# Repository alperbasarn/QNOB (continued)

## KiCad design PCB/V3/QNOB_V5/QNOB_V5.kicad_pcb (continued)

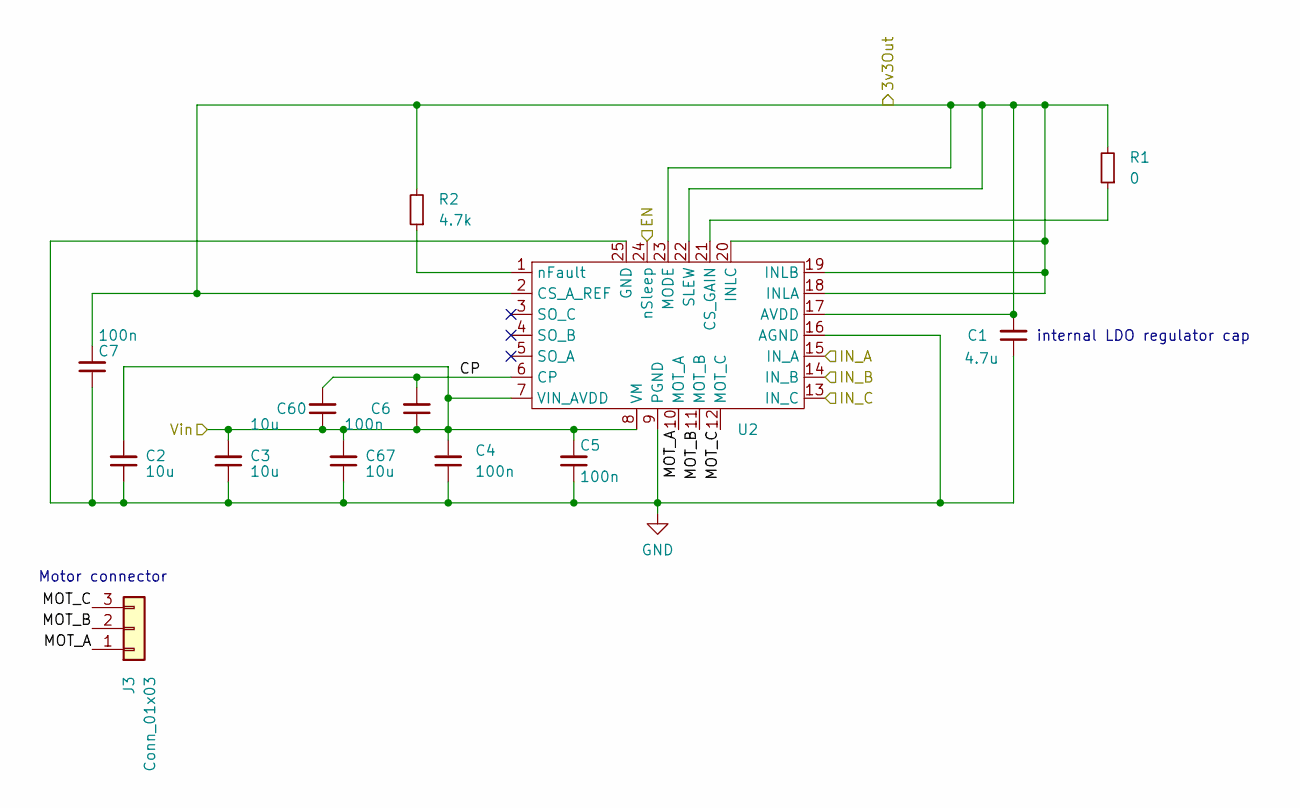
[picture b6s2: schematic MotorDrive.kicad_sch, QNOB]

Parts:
C1: 4.7u; C_0603_1608Metric_Pad1.08x0.95mm_HandSolder
C2, C3, C60: 10u; C_0603_1608Metric_Pad1.08x0.95mm_HandSolder
C4, C5, C6, C7: 100n; C_0603_1608Metric_Pad1.08x0.95mm_HandSolder
C67: 10u; CP_EIA-1608-08_AVX-J_Pad1.25x1.05mm_HandSolder
J3: Conn_01x03; Molex_PicoBlade_53048-0310_1x03_P1.25mm_Horizontal
R1: 0; R_0603_1608Metric_Pad0.98x0.95mm_HandSolder
R2: 4.7k; R_0603_1608Metric_Pad0.98x0.95mm_HandSolder
U2: IC_DRV8311HRRWR

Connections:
/GPIO5: U2.24 (nSleep); also elsewhere on the board
/GPIO6: U2.13 (IN_C); also elsewhere on the board
/GPIO7: U2.14 (IN_B); also elsewhere on the board
/GPIO8: U2.15 (IN_A); also elsewhere on the board
/Motor drive/CP: C6.2, C60.2, U2.6 (CP)
/Motor drive/MOT_A: J3.1, U2.10 (MOT_A)
/Motor drive/MOT_B: J3.2, U2.11 (MOT_B)
/Motor drive/MOT_C: J3.3, U2.12 (MOT_C)
DRV8311_3v3: C1.2, C7.2, R1.2, R2.2, U2.2 (CS_A_REF), U2.17 (AVDD), U2.18 (INLA), U2.19 (INLB), U2.20 (INLC), U2.22 (SLEW), U2.23 (MODE); also elsewhere on the board
GND: C1.1, C2.1, C3.1, C4.1, C5.1, C7.1, C67.1, U2.9 (PGND), U2.16 (AGND), U2.25 (GND); also elsewhere on the board
unnamed: R1.1, U2.21 (CS_GAIN)
unnamed: R2.1, U2.1 (nFault)
VSYS_PROTECTED: C2.2, C3.2, C4.2, C5.2, C6.1, C60.1, C67.2, U2.7 (VIN_AVDD), U2.8 (VM); also elsewhere on the board

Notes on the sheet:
Motor connector
internal LDO regulator cap

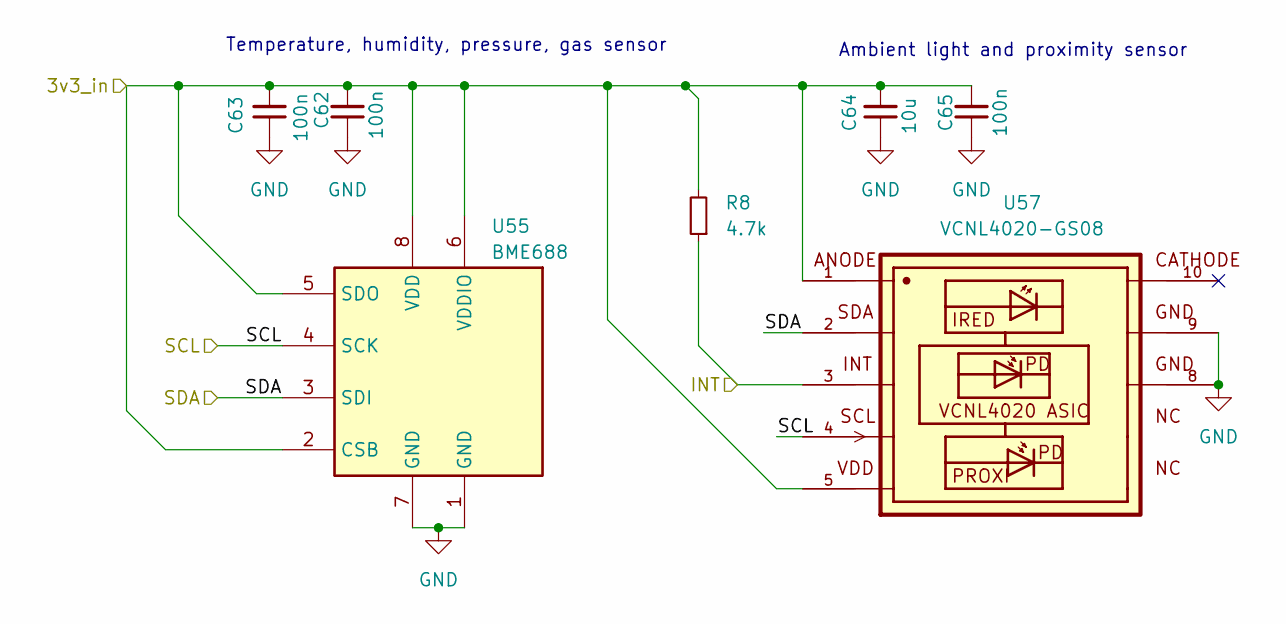
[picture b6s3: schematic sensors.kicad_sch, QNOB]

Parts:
C62, C63: 100n; C_0402_1005Metric
C64: 10u; C_0603_1608Metric_Pad1.08x0.95mm_HandSolder
C65: 100n; C_0603_1608Metric_Pad1.08x0.95mm_HandSolder
R8: 4.7k; R_0603_1608Metric_Pad0.98x0.95mm_HandSolder
U55: BME688; Bosch_LGA-8_3x3mm_P0.8mm_ClockwisePinNumbering
U57: VCNL4020-GS08; PHODET_VCNL4020

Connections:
3V3_Protected: C62.2, C63.2, C64.2, C65.2, R8.2, U55.2 (CSB), U55.5 (SDO), U55.6 (VDDIO), U55.8 (VDD), U57.1, U57.5; also elsewhere on the board
/GPIO1: R8.1, U57.3; also elsewhere on the board
/GPIO20: U55.4 (SCK), U57.4; also elsewhere on the board
/GPIO21: U55.3 (SDI), U57.2; also elsewhere on the board
GND: C62.1, C63.1, C64.1, C65.1, U55.1 (GND), U55.7 (GND), U57.8, U57.9; also elsewhere on the board

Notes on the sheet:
Ambient light and proximity sensor
Temperature, humidity, pressure, gas sensor

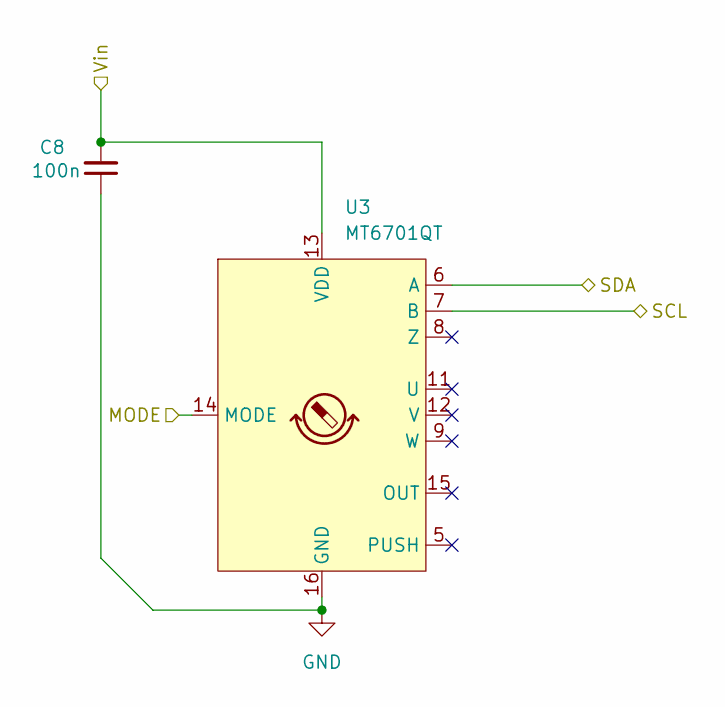
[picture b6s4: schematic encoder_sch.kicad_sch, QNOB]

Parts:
C8: 100n; C_0402_1005Metric
U3: MT6701QT; QFN-16-1EP_3x3mm_P0.5mm_EP1.7x1.7mm

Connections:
/ENC_POWER: C8.2, U3.13 (VDD); also elsewhere on the board
/GPIO20: U3.7 (B); also elsewhere on the board
/GPIO21: U3.6 (A); also elsewhere on the board
/encoder/MODE: U3.14 (MODE); also elsewhere on the board
GND: C8.1, U3.16 (GND), U3.17 (GND); also elsewhere on the board

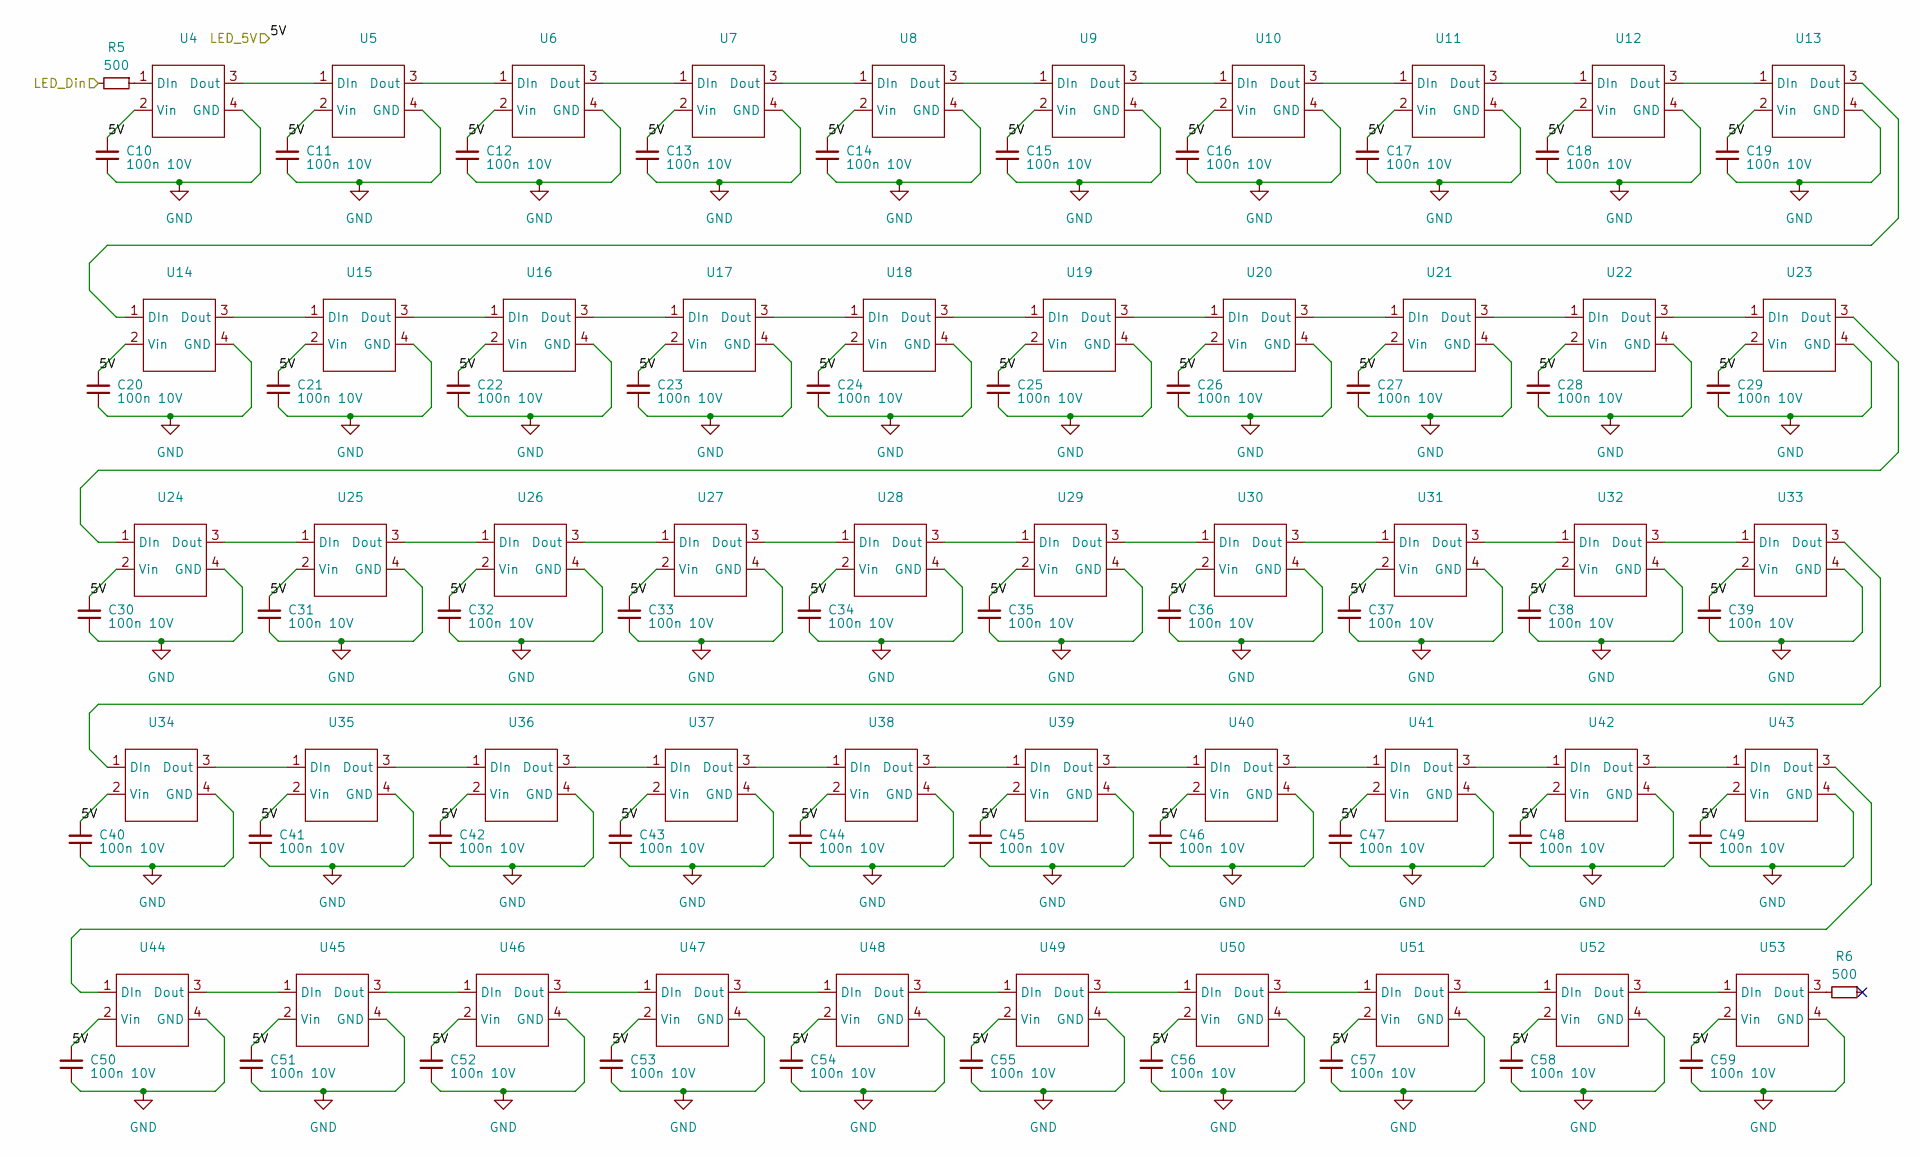
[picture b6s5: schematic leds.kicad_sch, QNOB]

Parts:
C10, C11, C12, C13, C14, C15, C16, C17, C18, C19, C20, C21, C22, C23, C24, C25, C26, C27, C28, C29, C30, C31, C32, C33, C34, C35, C36, C37, C38, C39, C40, C41, C42, C43, C44, C45, C46, C47, C48, C49, C50, C51, C52, C53, C54, C55, C56, C57, C58, C59: 100n 10V; C_0402_1005Metric
R5, R6: 500; R_0402_1005Metric
U4, U5, U6, U7, U8, U9, U10, U11, U12, U13, U14, U15, U16, U17, U18, U19, U20, U21, U22, U23, U24, U25, U26, U27, U28, U29, U30, U31, U32, U33, U34, U35, U36, U37, U38, U39, U40, U41, U42, U43, U44, U45, U46, U47, U48, U49, U50, U51, U52, U53: SK6805-EC15

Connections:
/leds/LED_Din: R5.2; also elsewhere on the board
GND: C10.1, C11.1, C12.1, C13.1, C14.1, C15.1, C16.1, C17.1, C18.1, C19.1, C20.1, C21.1, C22.1, C23.1, C24.1, C25.1, C26.1, C27.1, C28.1, C29.1, C30.1, C31.1, C32.1, C33.1, C34.1, C35.1, C36.1, C37.1, C38.1, C39.1, C40.1, C41.1, C42.1, C43.1, C44.1, C45.1, C46.1, C47.1, C48.1, C49.1, C50.1, C51.1, C52.1, C53.1, C54.1, C55.1, C56.1, C57.1, C58.1, C59.1, U4.4 (GND), U5.4 (GND), U6.4 (GND), U7.4 (GND), U8.4 (GND), U9.4 (GND), U10.4 (GND), U11.4 (GND), U12.4 (GND), U13.4 (GND), U14.4 (GND), U15.4 (GND), U16.4 (GND), U17.4 (GND), U18.4 (GND), U19.4 (GND), U20.4 (GND), U21.4 (GND), U22.4 (GND), U23.4 (GND), U24.4 (GND), U25.4 (GND), U26.4 (GND), U27.4 (GND), U28.4 (GND), U29.4 (GND), U30.4 (GND), U31.4 (GND), U32.4 (GND), U33.4 (GND), U34.4 (GND), U35.4 (GND), U36.4 (GND), U37.4 (GND), U38.4 (GND), U39.4 (GND), U40.4 (GND), U41.4 (GND), U42.4 (GND), U43.4 (GND), U44.4 (GND), U45.4 (GND), U46.4 (GND), U47.4 (GND), U48.4 (GND), U49.4 (GND), U50.4 (GND), U51.4 (GND), U52.4 (GND), U53.4 (GND); also elsewhere on the board
unnamed: R5.1, U4.1 (DIn)
unnamed: U4.3 (Dout), U5.1 (DIn)
unnamed: U5.3 (Dout), U6.1 (DIn)
unnamed: U6.3 (Dout), U7.1 (DIn)
unnamed: U7.3 (Dout), U8.1 (DIn)
unnamed: U8.3 (Dout), U9.1 (DIn)
unnamed: U9.3 (Dout), U10.1 (DIn)
unnamed: U10.3 (Dout), U11.1 (DIn)
unnamed: U11.3 (Dout), U12.1 (DIn)
unnamed: U12.3 (Dout), U13.1 (DIn)
unnamed: U13.3 (Dout), U14.1 (DIn)
unnamed: U14.3 (Dout), U15.1 (DIn)
unnamed: U15.3 (Dout), U16.1 (DIn)
unnamed: U16.3 (Dout), U17.1 (DIn)
unnamed: U17.3 (Dout), U18.1 (DIn)
unnamed: U18.3 (Dout), U19.1 (DIn)
unnamed: U19.3 (Dout), U20.1 (DIn)
unnamed: U20.3 (Dout), U21.1 (DIn)
unnamed: U21.3 (Dout), U22.1 (DIn)
unnamed: U22.3 (Dout), U23.1 (DIn)
unnamed: U23.3 (Dout), U24.1 (DIn)
unnamed: U24.3 (Dout), U25.1 (DIn)
unnamed: U25.3 (Dout), U26.1 (DIn)
unnamed: U26.3 (Dout), U27.1 (DIn)
unnamed: U27.3 (Dout), U28.1 (DIn)
unnamed: U28.3 (Dout), U29.1 (DIn)
unnamed: U29.3 (Dout), U30.1 (DIn)
unnamed: U30.3 (Dout), U31.1 (DIn)
unnamed: U31.3 (Dout), U32.1 (DIn)
unnamed: U32.3 (Dout), U33.1 (DIn)
unnamed: U33.3 (Dout), U34.1 (DIn)
unnamed: U34.3 (Dout), U35.1 (DIn)
unnamed: U35.3 (Dout), U36.1 (DIn)
unnamed: U36.3 (Dout), U37.1 (DIn)
unnamed: U37.3 (Dout), U38.1 (DIn)
unnamed: U38.3 (Dout), U39.1 (DIn)
unnamed: U39.3 (Dout), U40.1 (DIn)
unnamed: U40.3 (Dout), U41.1 (DIn)
unnamed: U41.3 (Dout), U42.1 (DIn)
unnamed: U42.3 (Dout), U43.1 (DIn)
unnamed: U43.3 (Dout), U44.1 (DIn)
unnamed: U44.3 (Dout), U45.1 (DIn)
unnamed: U45.3 (Dout), U46.1 (DIn)
unnamed: U46.3 (Dout), U47.1 (DIn)
unnamed: U47.3 (Dout), U48.1 (DIn)
unnamed: U48.3 (Dout), U49.1 (DIn)
unnamed: U49.3 (Dout), U50.1 (DIn)
unnamed: U50.3 (Dout), U51.1 (DIn)
unnamed: U51.3 (Dout), U52.1 (DIn)
unnamed: U52.3 (Dout), U53.1 (DIn)
unnamed: R6.2, U53.3 (Dout)
VSYS_PROTECTED: C10.2, C11.2, C12.2, C13.2, C14.2, C15.2, C16.2, C17.2, C18.2, C19.2, C20.2, C21.2, C22.2, C23.2, C24.2, C25.2, C26.2, C27.2, C28.2, C29.2, C30.2, C31.2, C32.2, C33.2, C34.2, C35.2, C36.2, C37.2, C38.2, C39.2, C40.2, C41.2, C42.2, C43.2, C44.2, C45.2, C46.2, C47.2, C48.2, C49.2, C50.2, C51.2, C52.2, C53.2, C54.2, C55.2, C56.2, C57.2, C58.2, C59.2, U4.2 (Vin), U5.2 (Vin), U6.2 (Vin), U7.2 (Vin), U8.2 (Vin), U9.2 (Vin), U10.2 (Vin), U11.2 (Vin), U12.2 (Vin), U13.2 (Vin), U14.2 (Vin), U15.2 (Vin), U16.2 (Vin), U17.2 (Vin), U18.2 (Vin), U19.2 (Vin), U20.2 (Vin), U21.2 (Vin), U22.2 (Vin), U23.2 (Vin), U24.2 (Vin), U25.2 (Vin), U26.2 (Vin), U27.2 (Vin), U28.2 (Vin), U29.2 (Vin), U30.2 (Vin), U31.2 (Vin), U32.2 (Vin), U33.2 (Vin), U34.2 (Vin), U35.2 (Vin), U36.2 (Vin), U37.2 (Vin), U38.2 (Vin), U39.2 (Vin), U40.2 (Vin), U41.2 (Vin), U42.2 (Vin), U43.2 (Vin), U44.2 (Vin), U45.2 (Vin), U46.2 (Vin), U47.2 (Vin), U48.2 (Vin), U49.2 (Vin), U50.2 (Vin), U51.2 (Vin), U52.2 (Vin), U53.2 (Vin); also elsewhere on the board

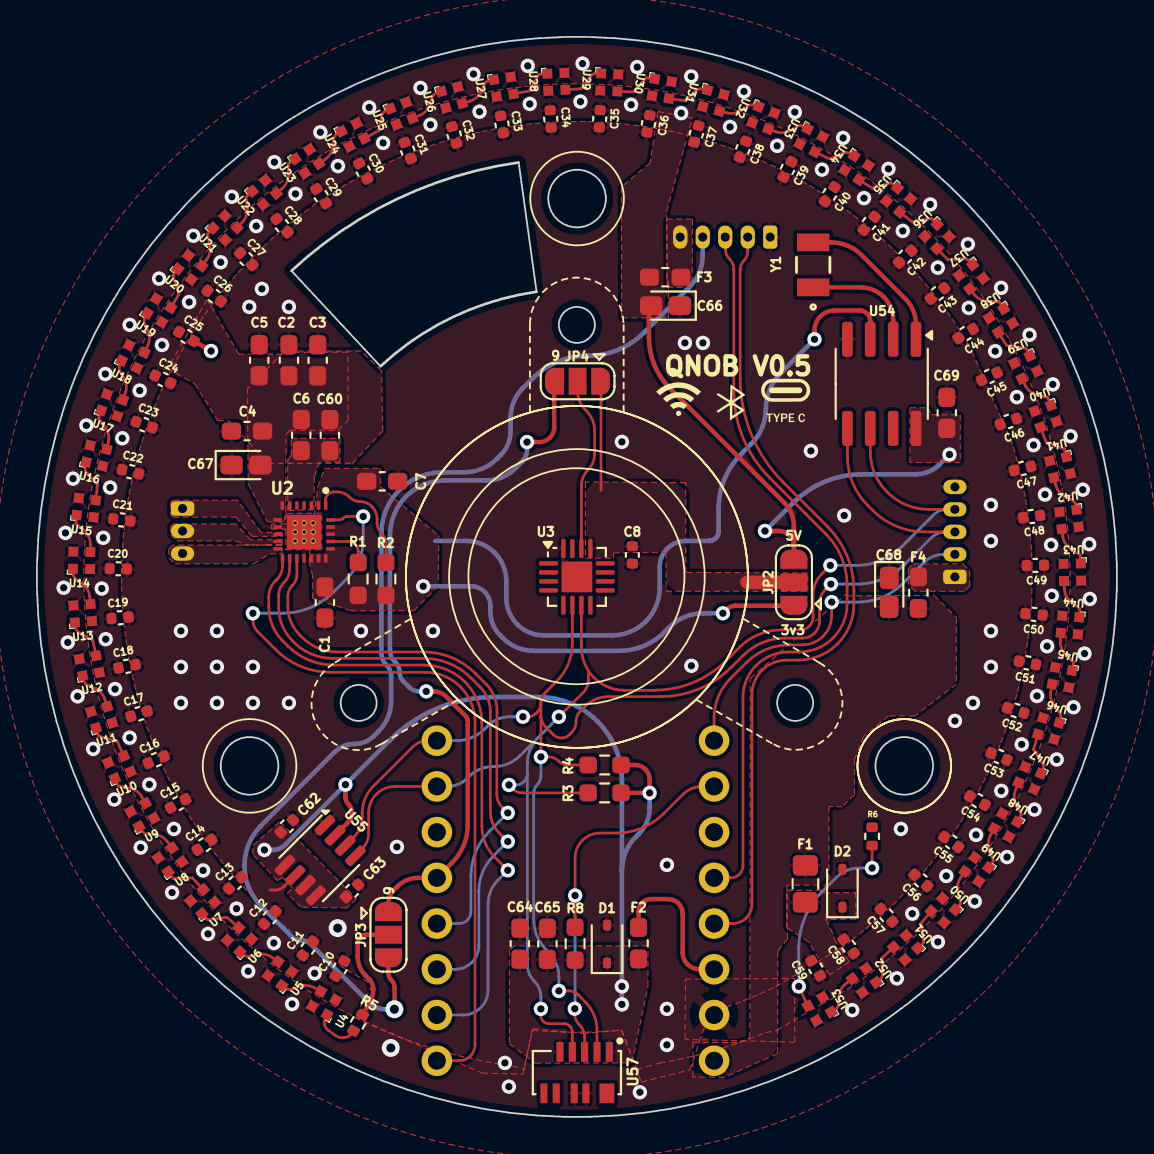
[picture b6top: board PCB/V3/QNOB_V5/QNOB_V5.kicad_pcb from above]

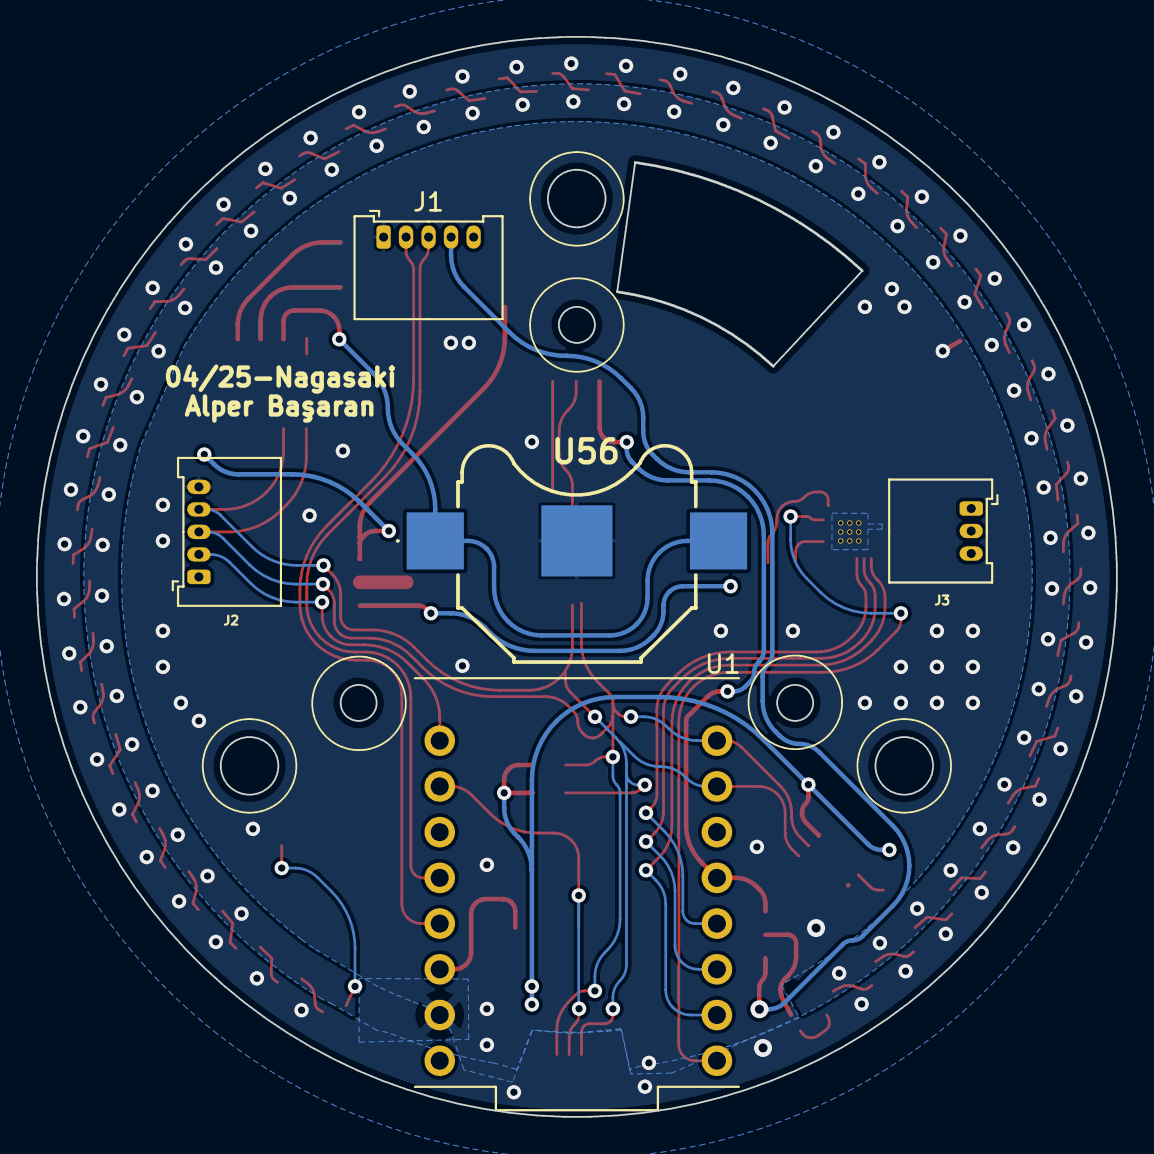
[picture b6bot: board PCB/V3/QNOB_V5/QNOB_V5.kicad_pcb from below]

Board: 2 copper layers, 60.0 x 60.0 mm, 144 parts (5 on the bottom side), 83 nets.

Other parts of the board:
C69: 100n; C_0603_1608Metric_Pad1.08x0.95mm_HandSolder
JP2, JP4: SolderJumper_3_Open; SolderJumper-3_P1.3mm_Open_RoundedPad1.0x1.5mm
U54: DS1307Z+; SOIC-8_3.9x4.9mm_P1.27mm
U56: battery_holder_1225_SMD
Y1: 32768 Hz; XTAL_FC-135_EPS

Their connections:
/ENC_POWER: JP2.2 (C), JP4.1 (A); also elsewhere on the board
/GPIO9: JP4.3 (B); also elsewhere on the board
/GPIO20: U54.6 (SCL); also elsewhere on the board
/GPIO21: U54.5 (SDA); also elsewhere on the board
/encoder/MODE: JP4.2 (C); also elsewhere on the board
DRV8311_3v3: JP2.1 (A); also elsewhere on the board
GND: C69.1, U54.4 (GND), U56.3 (-); also elsewhere on the board
unnamed: U54.3 (VBAT), U56.1 (+), U56.2 (+)
unnamed: U54.1 (X1), Y1.2
unnamed: U54.2 (X2), Y1.1
VSYS_PROTECTED: C69.2, JP2.3 (B), U54.8 (VCC); also elsewhere on the board

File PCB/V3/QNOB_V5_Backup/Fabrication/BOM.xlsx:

Comment | Designator | Footprint | LCSC Part #（optional）
4.7u | C1 | 603 | C19666
10u | C2 | 603 | C96446
10u | C3 | 603 | C96446
100n | C4 | 603 | C14663
100n | C5 | 603 | C14663
100n | C6 | 603 | C14663
100n | C7 | 603 | C14663
100n | C8 | 603 | C1525
100n 50V X7R | C10 | 402 | C1525
100n 50V X7R | C11 | 402 | C1525
100n 50V X7R | C12 | 402 | C1525
100n 50V X7R | C13 | 402 | C1525
100n 50V X7R | C14 | 402 | C1525
100n 50V X7R | C15 | 402 | C1525
100n 50V X7R | C16 | 402 | C1525
100n 50V X7R | C17 | 402 | C1525
100n 50V X7R | C18 | 402 | C1525
100n 50V X7R | C19 | 402 | C1525
100n 50V X7R | C20 | 402 | C1525
100n 50V X7R | C21 | 402 | C1525
100n 50V X7R | C22 | 402 | C1525
100n 50V X7R | C23 | 402 | C1525
100n 50V X7R | C24 | 402 | C1525
100n 50V X7R | C25 | 402 | C1525
100n 50V X7R | C26 | 402 | C1525
100n 50V X7R | C27 | 402 | C1525
100n 50V X7R | C28 | 402 | C1525
100n 50V X7R | C29 | 402 | C1525
100n 50V X7R | C30 | 402 | C1525
100n 50V X7R | C31 | 402 | C1525
100n 50V X7R | C32 | 402 | C1525
100n 50V X7R | C33 | 402 | C1525
100n 50V X7R | C34 | 402 | C1525
100n 50V X7R | C35 | 402 | C1525
100n 50V X7R | C36 | 402 | C1525
100n 50V X7R | C37 | 402 | C1525
100n 50V X7R | C38 | 402 | C1525
100n 50V X7R | C39 | 402 | C1525
100n 50V X7R | C40 | 402 | C1525
100n 50V X7R | C41 | 402 | C1525
100n 50V X7R | C42 | 402 | C1525
100n 50V X7R | C43 | 402 | C1525
100n 50V X7R | C44 | 402 | C1525
100n 50V X7R | C45 | 402 | C1525
100n 50V X7R | C46 | 402 | C1525
100n 50V X7R | C47 | 402 | C1525
100n 50V X7R | C48 | 402 | C1525
100n 50V X7R | C49 | 402 | C1525
100n 50V X7R | C50 | 402 | C1525
100n 50V X7R | C51 | 402 | C1525
100n 50V X7R | C52 | 402 | C1525
100n 50V X7R | C53 | 402 | C1525
100n 50V X7R | C54 | 402 | C1525
100n 50V X7R | C55 | 402 | C1525
100n 50V X7R | C56 | 402 | C1525
100n 50V X7R | C57 | 402 | C1525
100n 50V X7R | C58 | 402 | C1525
100n 50V X7R | C59 | 402 | C1525
10u | C60 | 603 | C96446
100n | C62 | 603 | C14663
100n | C63 | 603 | C14663
10u | C64 | 603 | C96446
100n | C65 | 603 | C14663
10u | C66 | 603 | C96446
10u | C67 | 603 | C96446
10u | C68 | 603 | C96446
100n | C69 | 603 | C14663
D_SOD-323 | D1 | SMT | C344002
D_SOD-323 | D2 | SMT | C344002
500mA | F1 | SMT | C20976
500mA | F2 | SMT | C20785
500mA | F3 | SMT | C20785
500mA | F4 | SMT | C20785
0 | R1 | 603 | C21189
4.7k | R2 | 603 | C23162
4.7k | R3 | 603 | C23162
4.7k | R4 | 603 | C23162
2k | R5 | 402 | C4109
2k | R6 | 402 | C4109
4.7k | R8 | 603 | C23162
DRV8311HRRWR | U2 | WQFN-24(3x3) | C5218862
MT6701CT | U3 | SOP-8 | C2913974
Adressable RGB LED | U4 | 606 | C2890035
Adressable RGB LED | U5 | 606 | C2890035
Adressable RGB LED | U6 | 606 | C2890035
Adressable RGB LED | U7 | 606 | C2890035
Adressable RGB LED | U8 | 606 | C2890035
Adressable RGB LED | U9 | 606 | C2890035
Adressable RGB LED | U10 | 606 | C2890035
Adressable RGB LED | U11 | 606 | C2890035
Adressable RGB LED | U12 | 606 | C2890035
Adressable RGB LED | U13 | 606 | C2890035
Adressable RGB LED | U14 | 606 | C2890035
Adressable RGB LED | U15 | 606 | C2890035
Adressable RGB LED | U16 | 606 | C2890035
Adressable RGB LED | U17 | 606 | C2890035
Adressable RGB LED | U18 | 606 | C2890035
Adressable RGB LED | U19 | 606 | C2890035
Adressable RGB LED | U20 | 606 | C2890035
Adressable RGB LED | U21 | 606 | C2890035
Adressable RGB LED | U22 | 606 | C2890035
Adressable RGB LED | U23 | 606 | C2890035
Adressable RGB LED | U24 | 606 | C2890035
Adressable RGB LED | U25 | 606 | C2890035
Adressable RGB LED | U26 | 606 | C2890035
Adressable RGB LED | U27 | 606 | C2890035
Adressable RGB LED | U28 | 606 | C2890035
Adressable RGB LED | U29 | 606 | C2890035
Adressable RGB LED | U30 | 606 | C2890035
Adressable RGB LED | U31 | 606 | C2890035
Adressable RGB LED | U32 | 606 | C2890035
Adressable RGB LED | U33 | 606 | C2890035
Adressable RGB LED | U34 | 606 | C2890035
Adressable RGB LED | U35 | 606 | C2890035
Adressable RGB LED | U36 | 606 | C2890035
Adressable RGB LED | U37 | 606 | C2890035
Adressable RGB LED | U38 | 606 | C2890035
Adressable RGB LED | U39 | 606 | C2890035
Adressable RGB LED | U40 | 606 | C2890035
Adressable RGB LED | U41 | 606 | C2890035
Adressable RGB LED | U42 | 606 | C2890035
Adressable RGB LED | U43 | 606 | C2890035
Adressable RGB LED | U44 | 606 | C2890035
Adressable RGB LED | U45 | 606 | C2890035
Adressable RGB LED | U46 | 606 | C2890035
Adressable RGB LED | U47 | 606 | C2890035
Adressable RGB LED | U48 | 606 | C2890035
Adressable RGB LED | U49 | 606 | C2890035
Adressable RGB LED | U50 | 606 | C2890035
Adressable RGB LED | U51 | 606 | C2890035
Adressable RGB LED | U52 | 606 | C2890035
Adressable RGB LED | U53 | 606 | C2890035
RTC | U54 | 606 | C26858
Environment sensor | U55 | SMT | C3664478
Lux sensor | U57 | SMT | C511034
32768 crystal | Y1 | 3215-2p | C32346

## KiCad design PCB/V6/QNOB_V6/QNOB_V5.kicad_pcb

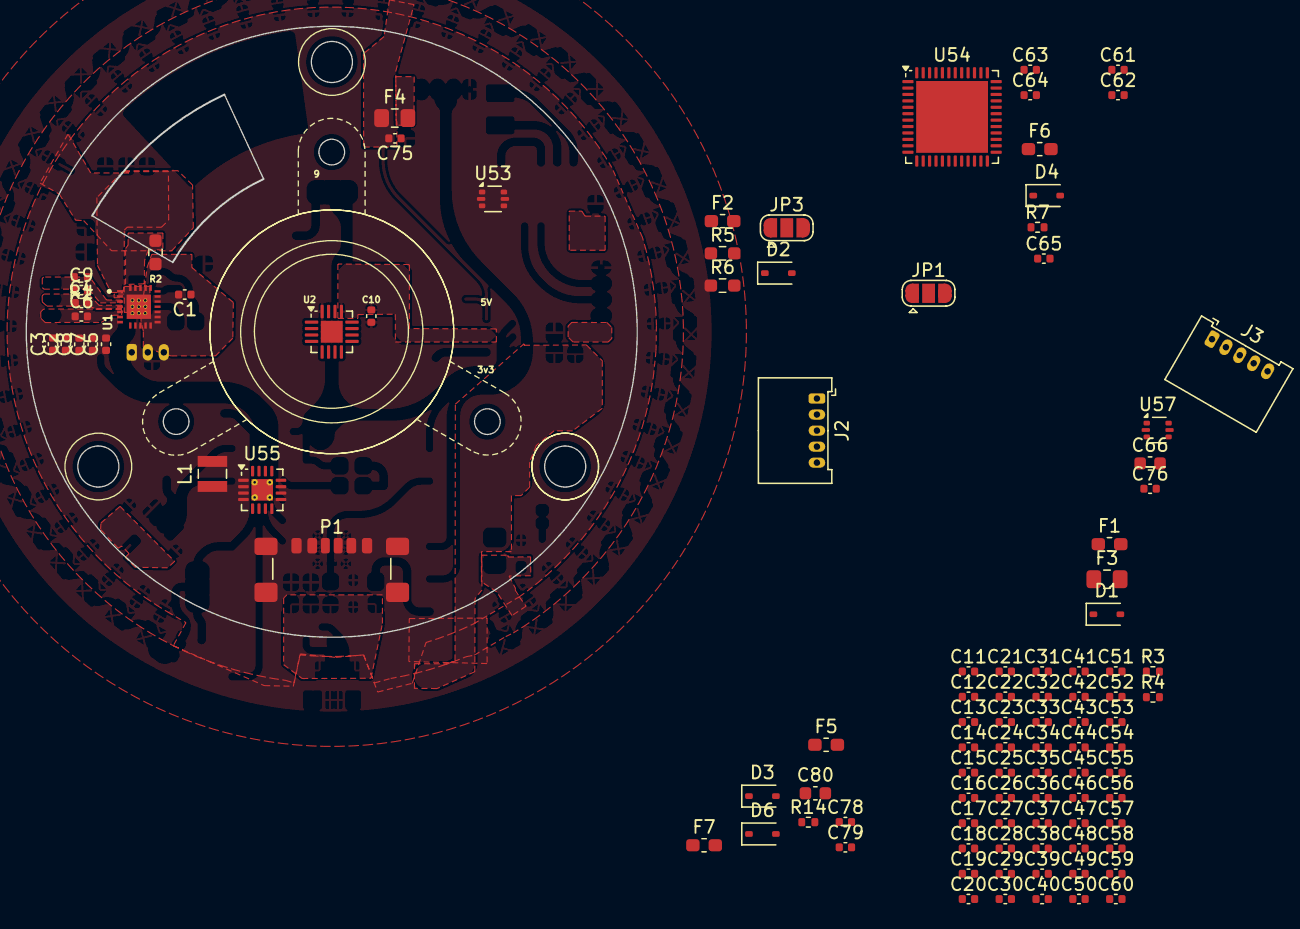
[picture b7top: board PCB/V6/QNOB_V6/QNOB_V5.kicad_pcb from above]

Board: 2 copper layers, 47.6 x 47.6 mm, 104 parts (1 on the bottom side), 31 nets, no tracks yet.

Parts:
C1, C2, C4, C5, C6, C7, C64, C75, C76, C78: 10u; C_0402_1005Metric
C3, C8, C9, C10, C12: 100n; C_0402_1005Metric
C11: 4.7u; C_0402_1005Metric
C13, C14, C15, C16, C17, C18, C19, C20, C21, C22, C23, C24, C25, C26, C27, C28, C29, C30, C31, C32, C33, C34, C35, C36, C37, C38, C39, C40, C41, C42, C43, C44, C45, C46, C47, C48, C49, C50, C51, C52, C53, C54, C55, C56, C57, C58, C59, C60, C61, C62: 100n 10V; C_0402_1005Metric
C63: 1u; C_0402_1005Metric
C65, C79: 3.3n; C_0402_1005Metric
C66, C80: 22u; C_0603_1608Metric
D1, D2, D3, D4, D6: ESD5Zxx; D_SOD-323
F1, F2, F5: 500m; Fuse_0603_1608Metric_Pad1.05x0.95mm_HandSolder
F3: 2.5A; Fuse_0805_2012Metric_Pad1.15x1.40mm_HandSolder
F4: 1A; Fuse_0805_2012Metric_Pad1.15x1.40mm_HandSolder
F6, F7: 200mA; Fuse_0603_1608Metric_Pad1.05x0.95mm_HandSolder
J1: Conn_01x03; Molex_PicoBlade_53048-0310_1x03_P1.25mm_Horizontal
J2, J3: Conn_01x05; Molex_PicoBlade_53048-0510_1x05_P1.25mm_Horizontal
JP1, JP3: SolderJumper_3_Open; SolderJumper-3_P1.3mm_Open_RoundedPad1.0x1.5mm
L1: 2.2u; L_Wuerth_MAPI-2506
P1: USB_C_Plug_USB2.0; USB_C_Receptacle_GCT_USB4135-GF-A_6P_TopMnt_Horizontal
R1: 4.7k; R_0402_1005Metric
R2: 0; R_0603_1608Metric_Pad0.98x0.95mm_HandSolder
R3, R4: 500; R_0402_1005Metric
R5, R6: 4.7k; R_0603_1608Metric_Pad0.98x0.95mm_HandSolder
R7, R14: 100k; R_0402_1005Metric
U1: IC_DRV8311HRRWR
U2: MT6701QT; QFN-16-1EP_3x3mm_P0.5mm_EP1.7x1.7mm
U53, U57: USBLC6-2P6; SOT-666
U54: STM32F401CBUx; QFN-48-1EP_7x7mm_P0.5mm_EP5.6x5.6mm
U55: TPS62130; VQFN-16-1EP_3x3mm_P0.5mm_EP1.68x1.68mm_ThermalVias

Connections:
3V3: F6.2, F7.2
3V3_Protected: D3.1 (K), F5.2, R5.2, R6.2
5V: C2.2, C76.2, F1.1
/DRV8311_3v3: C3.2, C11.2, R1.2, R2.2, U1.2 (CS_A_REF), U1.17 (AVDD), U1.18 (INLA), U1.19 (INLB), U1.20 (INLC), U1.22 (SLEW), U1.23 (MODE)
/ENC_POWER: C12.2, U2.13 (VDD)
/GPIO9: JP1.1 (A), JP3.1 (A)
/GPIO20: J2.4, U2.7 (B)
/GPIO21: J2.3, U2.6 (A)
/LED_CTRL: J3.4, JP1.3 (B), JP3.3 (B)
/MCU/D+: U53.4 (I/O2), U57.4 (I/O2)
/MCU/D-: U53.6 (I/O1), U57.6 (I/O1)
/Motor drive/CP: C6.2, C8.2, U1.6 (CP)
/leds/LED_Din: JP1.2 (C), JP3.2 (C), R3.2
GND: C1.1, C2.1, C3.1, C4.1, C5.1, C7.1, C9.1, C10.1, C11.1, C12.1, C13.1, C14.1, C15.1, C16.1, C17.1, C18.1, C19.1, C20.1, C21.1, C22.1, C23.1, C24.1, C25.1, C26.1, C27.1, C28.1, C29.1, C30.1, C31.1, C32.1, C33.1, C34.1, C35.1, C36.1, C37.1, C38.1, C39.1, C40.1, C41.1, C42.1, C43.1, C44.1, C45.1, C46.1, C47.1, C48.1, C49.1, C50.1, C51.1, C52.1, C53.1, C54.1, C55.1, C56.1, C57.1, C58.1, C59.1, C60.1, C61.1, C62.1, C63.1, C66.2, C75.1, C76.1, C80.2, D1.2 (A), D2.2 (A), D3.2 (A), D4.2 (A), D6.2 (A), J2.5, J3.1, P1.A12 (GND), P1.B12 (GND), P1.S1 (SHIELD), R7.1, R14.1, U1.9 (PGND), U1.16 (AGND), U1.25 (GND), U2.16 (GND), U2.17 (GND), U53.2 (GND), U55.4 (PG), U55.5 (FB), U55.6 (GND), U55.15 (GND), U55.16 (GND), U55.17 (GND), U57.2 (GND)
unnamed: C63.2, D1.1 (K), F3.2, U53.5 (VBUS)
unnamed: C66.1, D4.1 (K), F6.1, L1.2, R7.2, U55.14 (VOS)
unnamed: C80.1, D6.1 (K), F7.1, R14.2
unnamed: F1.2, J2.1
unnamed: F2.2, J3.5
unnamed: L1.1, U55.1 (SW), U55.2 (SW), U55.3 (SW)
unnamed: U53.3 (I/O2), U57.3 (I/O2)
unnamed: U53.1 (I/O1), U57.1 (I/O1)
unnamed: R2.1, U1.21 (CS_GAIN)
unnamed: R1.1, U1.1 (nFault)
unnamed: U54.23 (VSS), U54.35 (VSS), U54.47 (VSS), U54.49 (VSS)
unnamed: C64.1, C65.2, U55.7 (FSW), U55.8 (DEF)
unnamed: C64.2, U55.10 (VIN), U55.11 (VIN), U55.12 (VIN), U55.13 (EN)
unnamed: C65.1, U55.9 (SS/TR)
unnamed: C78.1, C79.2
VBUS: F3.1, P1.A9 (VBUS), P1.B9 (VBUS)
VSYS_PROTECTED: C1.2, C4.2, C5.2, C6.1, C7.2, C8.1, C9.2, C10.2, C13.2, C14.2, C15.2, C16.2, C17.2, C18.2, C19.2, C20.2, C21.2, C22.2, C23.2, C24.2, C25.2, C26.2, C27.2, C28.2, C29.2, C30.2, C31.2, C32.2, C33.2, C34.2, C35.2, C36.2, C37.2, C38.2, C39.2, C40.2, C41.2, C42.2, C43.2, C44.2, C45.2, C46.2, C47.2, C48.2, C49.2, C50.2, C51.2, C52.2, C53.2, C54.2, C55.2, C56.2, C57.2, C58.2, C59.2, C60.2, C61.2, C62.2, C75.2, D2.1 (K), F2.1, F4.2, U1.7 (VIN_AVDD), U1.8 (VM)

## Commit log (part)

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2025-03-16 initial commit with touch screen firmware
2025-03-18 create independent handlers for time and weather
2025-03-24 before refactoring screen.ino
2025-03-25 kinda stable
2025-03-28 created arc class
    added py program for PC UI
2025-03-28 modularize python UI
2025-03-28 add mqtt subtab
2025-03-28 modularize terminal class
2025-03-28 add documents and gitignore
2025-03-28 fix folder structure
2025-03-28 add widgets to terminals
2025-04-05 continue refactor
2025-04-05 debug
2025-05-01 add pcb's
2025-05-01 add 3d design
2025-05-13 move versions
2026-01-24 add latest items
2026-01-25 remove breakout projects
2026-02-01 start refactor
